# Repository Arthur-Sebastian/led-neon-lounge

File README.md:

# LED Lounge Neon!
An RGB LED neon project using 3d printed parts and custom AVR-based controller board with included software.

## PCB
Printed circuit board design (one-layer) files can be found inside ['/pcb'](/pcb). It was created in KiCad open-source
EDA.
The design includes all the parts names,
package formats, and source schematic. It can all be found by opening ['pcb.pro'](/pcb/pcb.pro). file.

## AVR source code and binary
The controller board uses a popular MCU, an ATmega168p. Software source can be found inside ['/src'](/src).
Compile using the included shell script, or create a makefile for yourself. The binary file ['/src/bin/out.bin'](/src/bin/out.bin)
can be directly uploaded to a matching MCU by using the 'upload.sh' script - it assumes your serial-usb converter is connected to
/dev/ttyUSB0 and that your MCU has a USART capable bootloader. Modify if needed.

## 3D Models for printing
Can be found inside ['/resource_3d'](/resource_3d). Those are all Blender files. 
All necessary STL exports are already made and contained within stl_* folders. 
Slice using your favourite tool, and print! 
(All models are optimised to fit a PRUSA Mini or bigger - min. work area of 175 x 175 x 175mm).

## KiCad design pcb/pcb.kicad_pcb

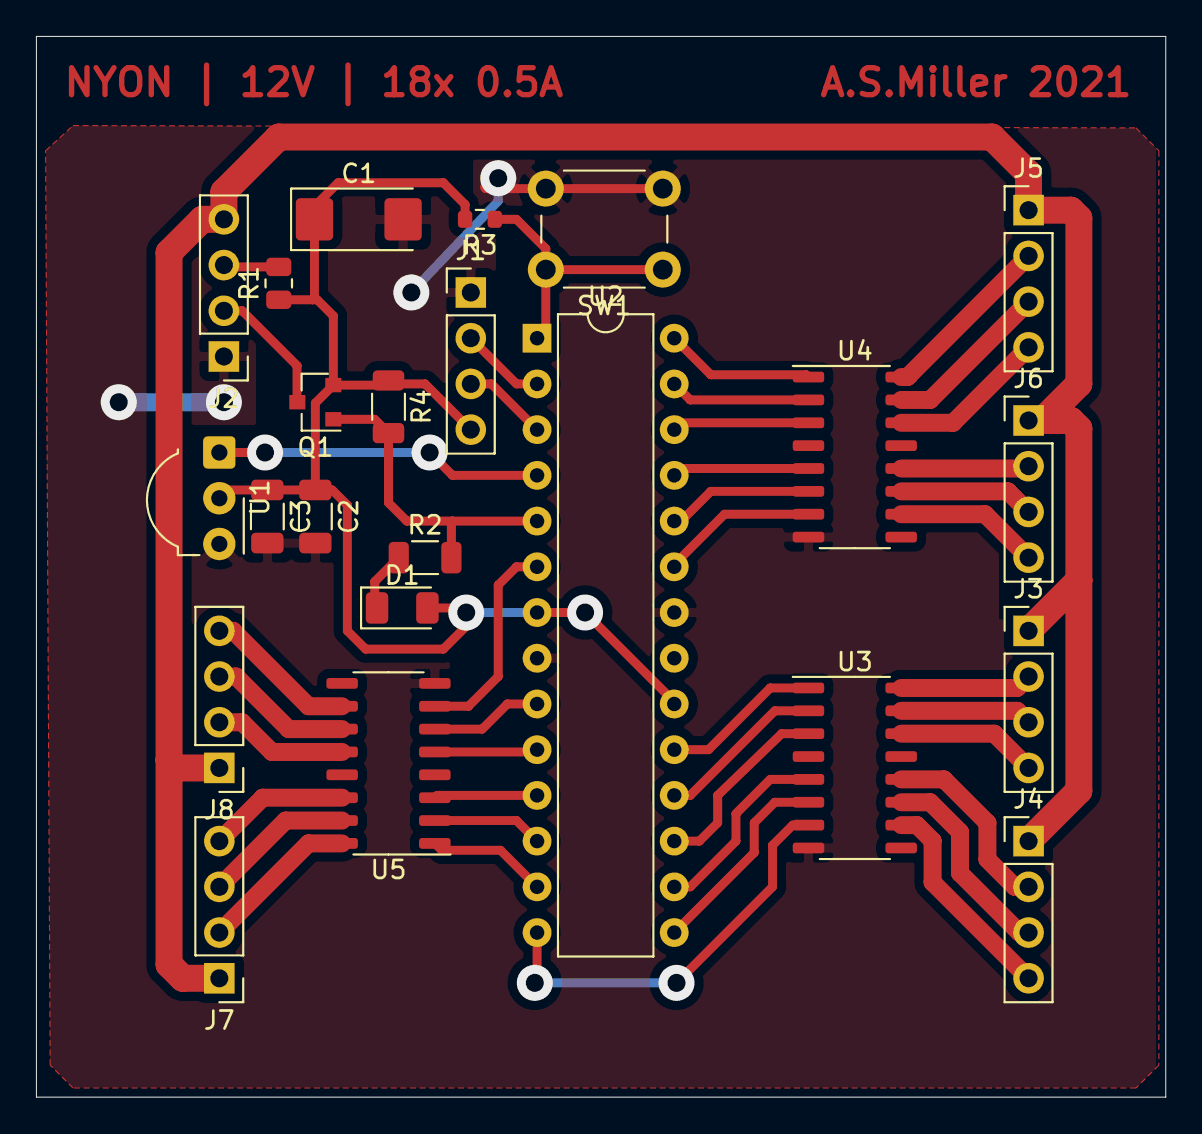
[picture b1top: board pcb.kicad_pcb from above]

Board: 2 copper layers, 62.7 x 58.9 mm, 23 parts (0 on the bottom side), 47 nets.

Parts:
C1: 470uF; CP_EIA-6032-20_AVX-F
C2, C3: CP; C_1206_3216Metric
D1: LED; LED_1206_3216Metric
J1, J2, J3, J4, J5, J6, J7, J8: Conn_01x04_Female; PinHeader_1x04_P2.54mm_Vertical
Q1: Q_PMOS_GSD; SOT-23
R1: 4.7; R_0805_2012Metric
R2: 1.8k; R_1206_3216Metric
R3: 10k; R_0603_1608Metric
R4: 1k; R_1206_3216Metric
SW1: SW_SPST; SW_PUSH_6mm_H4.3mm
U1: TSOP21xx; Vishay_MOLD-3Pin
U2: ATmega168PA-PU; DIP-28_W7.62mm
U3, U4, U5: ULN2003; SO-16_3.9x9.9mm_P1.27mm

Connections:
5VDC: C1.1, C2.1, C3.1, D1.2, J1.4, Q1.2, R1.1, R3.2, R4.1, U1.2, U2.7, U2.20
+5V: J2.3, R1.2
+12V: J2.4, J3.1, J4.1, J5.1, J6.1, J7.1, J8.1
GND: C1.2, C2.2, C3.2, J1.1, J2.1, SW1.2, U1.3, U2.8, U2.22, U3.8, U4.8, U5.8
IR: U1.1, U2.4
unnamed: D1.1, R2.1
unnamed: J3.2, U3.16
unnamed: J3.3, U3.15
unnamed: J3.4, U3.14
unnamed: J4.2, U3.12
unnamed: J4.3, U3.11
unnamed: J4.4, U3.10
unnamed: J5.2, U4.16
unnamed: J5.3, U4.15
unnamed: J5.4, U4.14
unnamed: J6.2, U4.12
unnamed: J6.3, U4.11
unnamed: J6.4, U4.10
unnamed: J7.2, U5.16
unnamed: J7.3, U5.15
unnamed: J7.4, U5.14
unnamed: J8.2, U5.12
unnamed: J8.3, U5.11
unnamed: J8.4, U5.10
unnamed: U2.6, U5.7
unnamed: U2.9, U5.6
unnamed: U2.10, U5.5
unnamed: U2.11, U5.3
unnamed: U2.12, U5.2
unnamed: U2.13, U5.1
unnamed: U2.14, U3.7
unnamed: U2.15, U3.6
unnamed: U2.16, U3.5
unnamed: U2.17, U3.3
unnamed: U2.18, U3.2
unnamed: U2.19, U3.1
unnamed: U2.23, U4.7
unnamed: U2.24, U4.6
unnamed: U2.25, U4.5
unnamed: U2.26, U4.3
unnamed: U2.27, U4.2
unnamed: U2.28, U4.1
PWR: J2.2, Q1.3
PWR_EN: Q1.1, R2.2, R4.2, U2.5
RST: R3.1, SW1.1, U2.1
RXD: J1.3, U2.3
TXD: J1.2, U2.2

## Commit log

2021-12-19 Uploaded archive files
2021-12-19 Minor fixes
2021-12-19 Readme improvements
2021-12-19 Added license
2022-08-05 migrate to atmega328p
2023-09-02 feat: add static color modifiers
